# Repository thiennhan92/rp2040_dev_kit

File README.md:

# RP2040 Development Board

This is a custom development board based on the Raspberry Pi RP2040 microcontroller. It integrates essential peripherals for embedded systems prototyping, including USB, Ethernet, RGB LEDs, sensors, and storage. The design is accompanied by validated firmware that supports all core hardware features.

---

## 🧩 Features

- **Microcontroller**: Raspberry Pi RP2040 (dual-core ARM Cortex-M0+)
- **Power Management**:
  - XL1509-3.3 Buck Converter
  - CH217K USB Power Switch
- **USB Interface**:
  - CH340N USB-to-Serial
  - Dual USB ports for host and device roles
- **Networking**:
  - LAN8720A Ethernet PHY (RMII)
  - RJ45 connector (HR911105A)
- **Storage**:
  - MicroSD card 
  - W25Q128FV QSPI Flash
- **Sensors**:
  - ADXL345 3-Axis Accelerometer (I²C/SPI configurable)
- **User Interface**:
  - Daisy-chained WS2812-compatible RGB LEDs
  - Onboard buzzer
  - Status LEDs (Ethernet activity)
- **Debugging**:
  - SWD interface
  - USB bootloader support
- **Expansion**:
  - HDMI-style connector (repurposed for GPIO)
  - Multiple GPIO headers and DIP switches

---

## ✅ Firmware Validation

The firmware has been **fully validated** and supports all major board features.  
*(Please check with Arduino and Pico SDK examples)*

The firmware has been fully validated and supports all major board features:

- [x] **USB Host/Device** – Detection and communication
- [x] **Ethernet** – Connectivity via LAN8720A
- [x] **MicroSD** – FAT filesystem read/write
- [x] **RGB LEDs** – WS2812-compatible LED control
- [x] **ADXL345** – Sensor readout over I²C
- [x] **QSPI Flash** – W25Q128FV access
- [x] **Buzzer & GPIO** – Output control and signal handling
- [x] **HDMI** - Digital video signal rendering tested
- [x] **Bootloader & SWD** – Debugging and firmware upload

© 2025 – RP2040 Dev Board Project. All rights reserved.

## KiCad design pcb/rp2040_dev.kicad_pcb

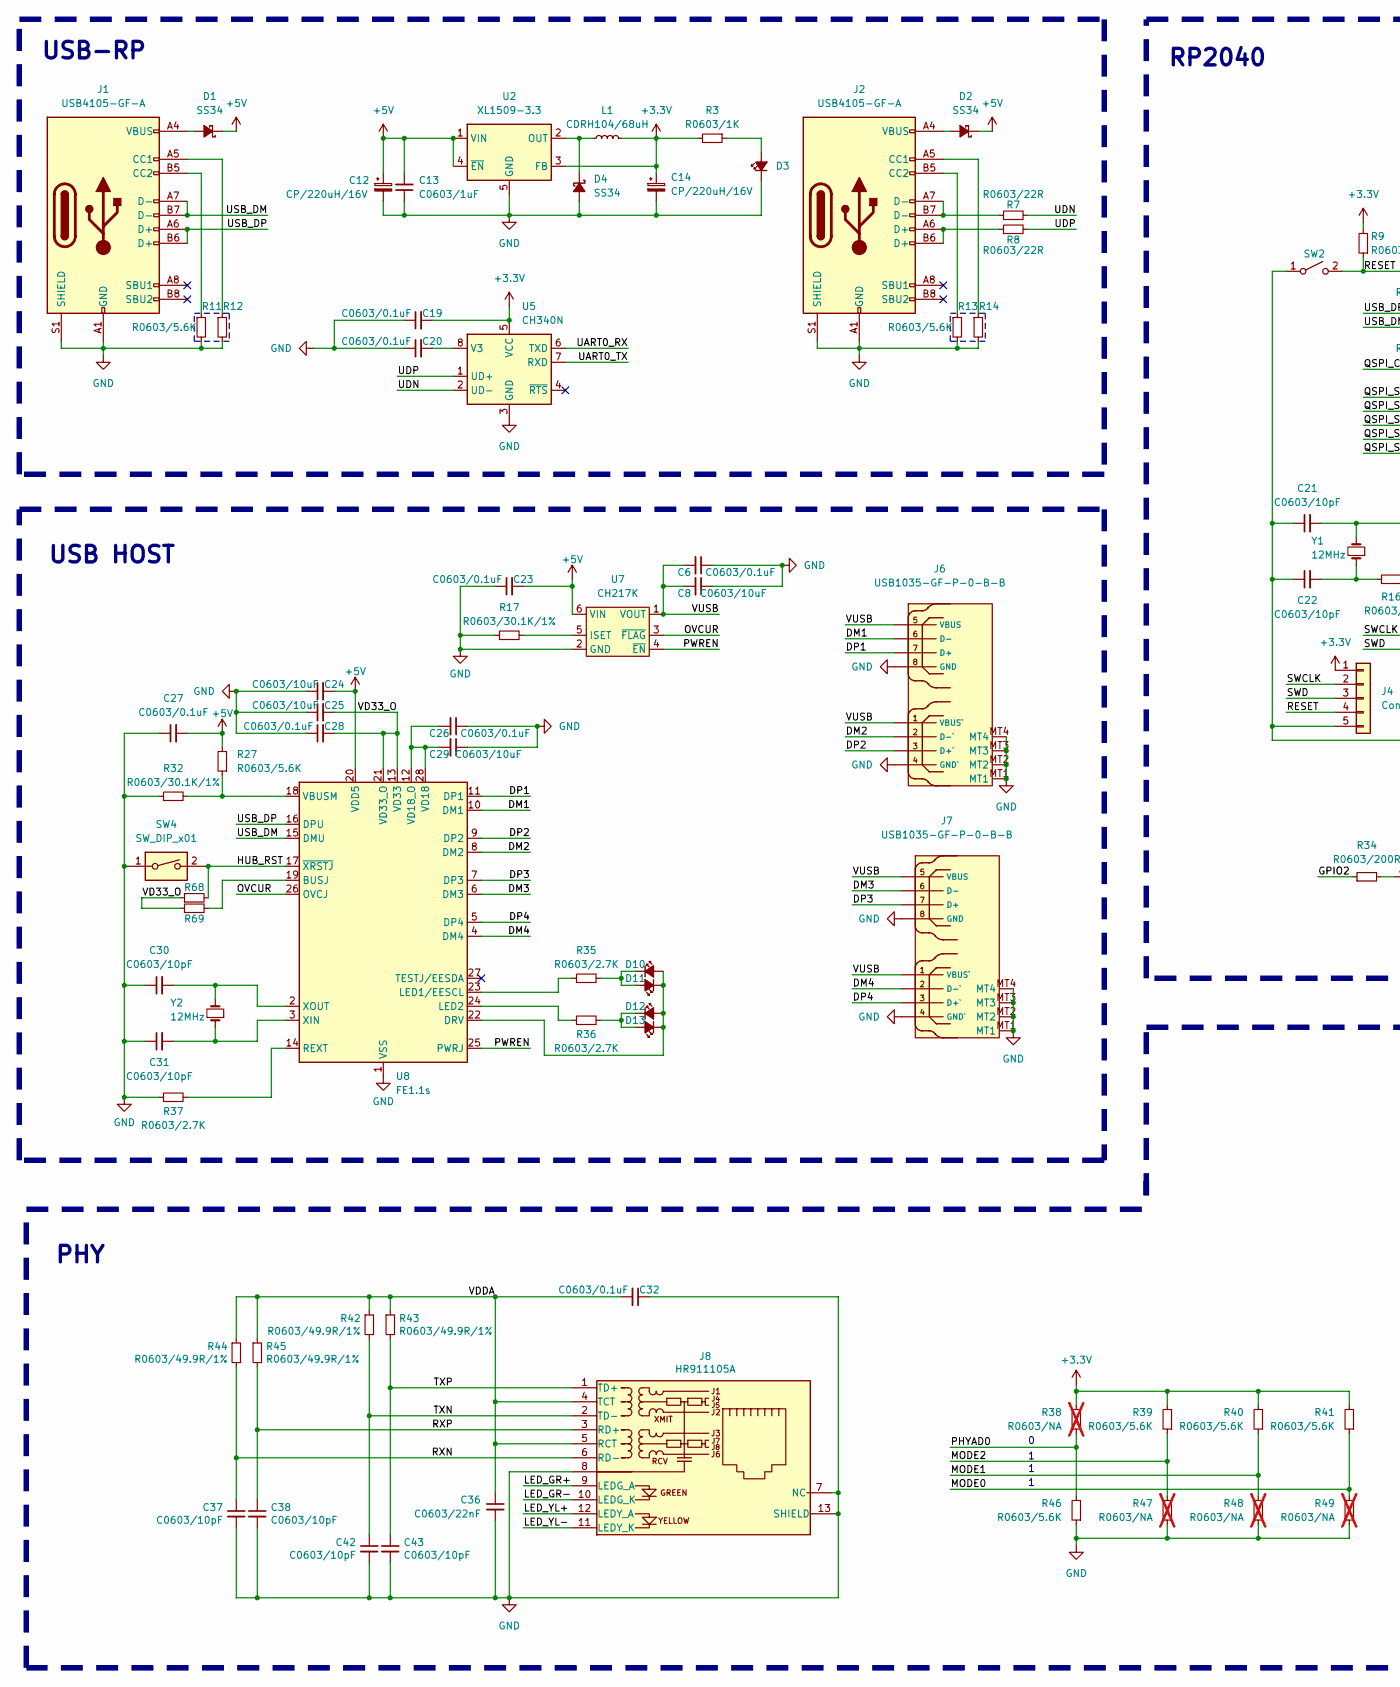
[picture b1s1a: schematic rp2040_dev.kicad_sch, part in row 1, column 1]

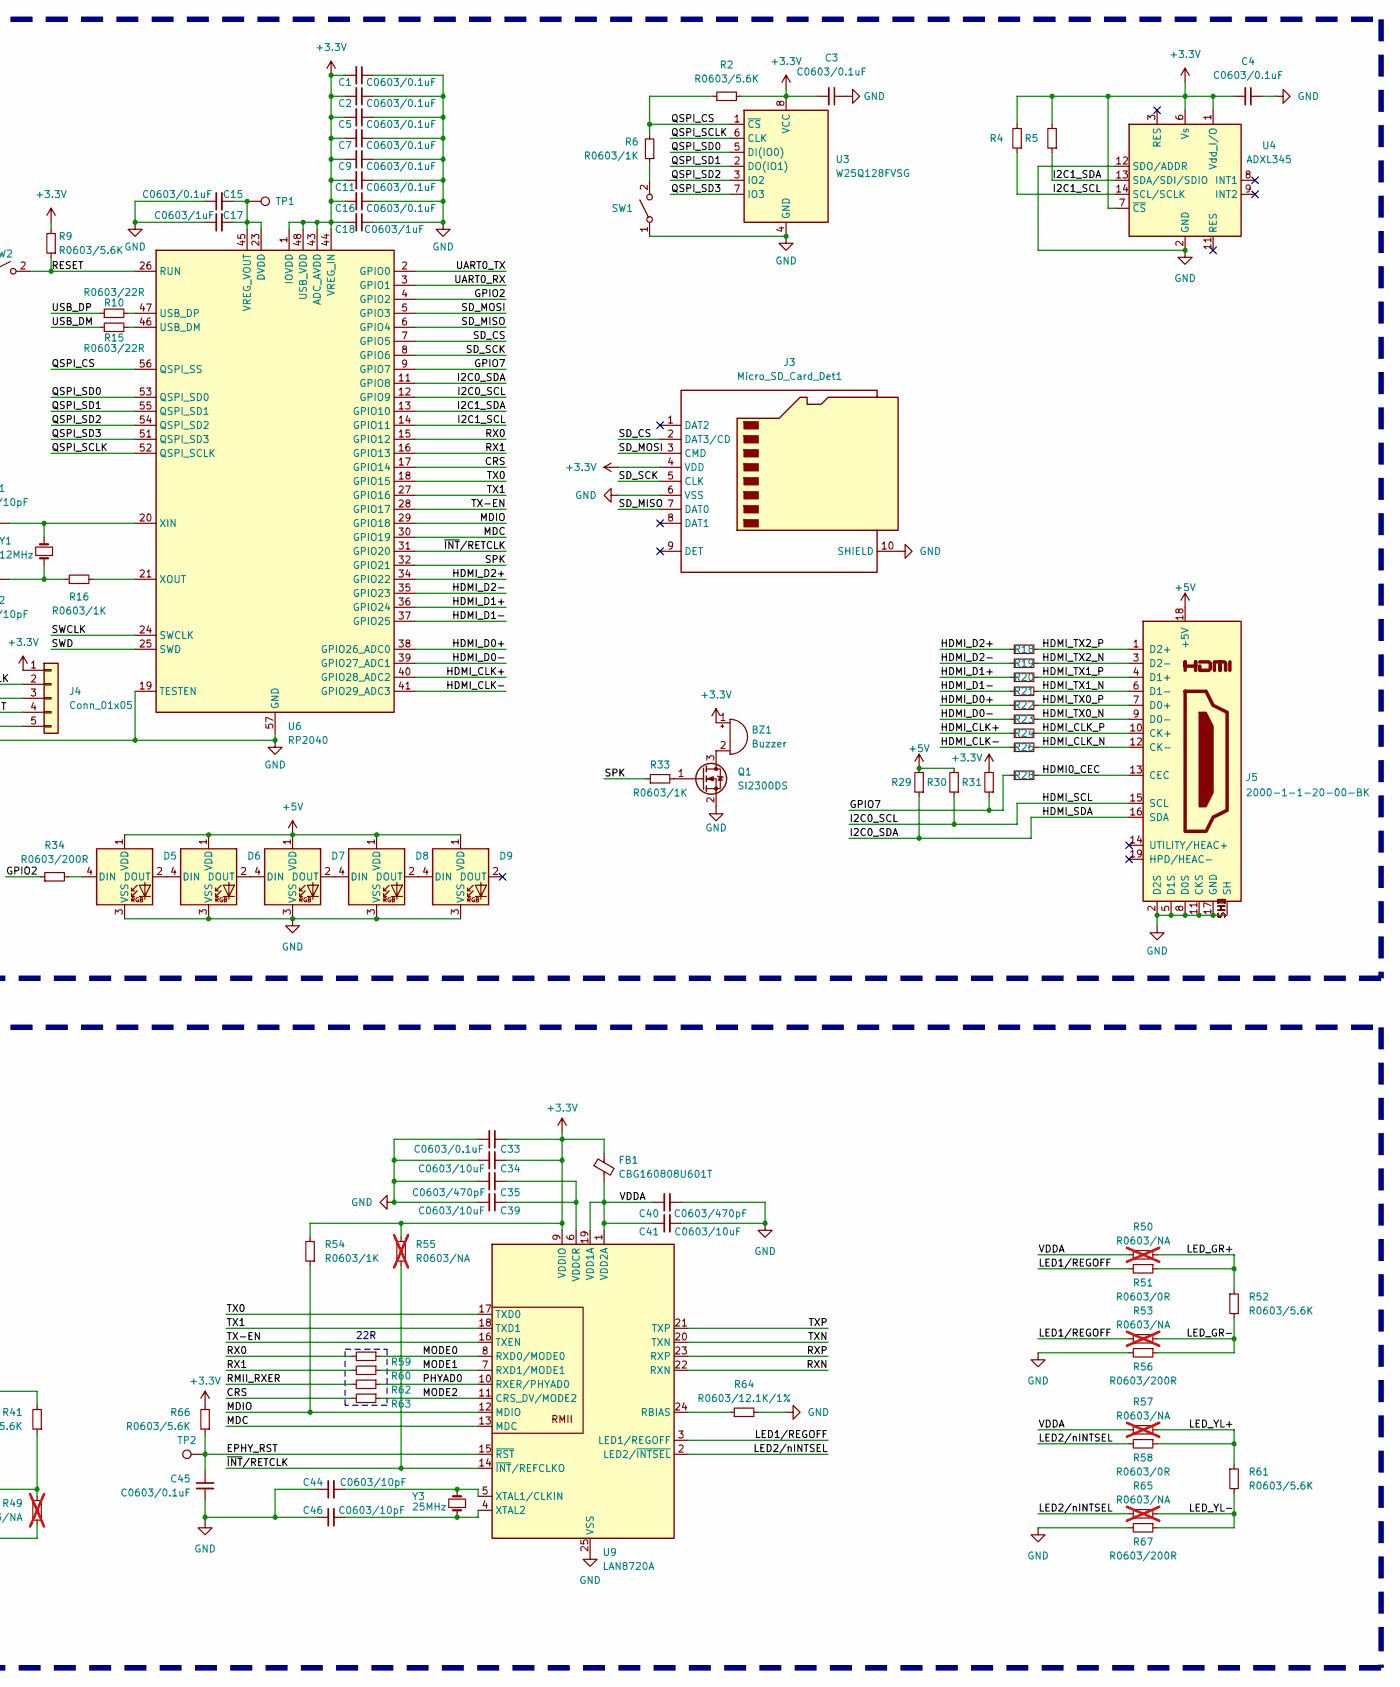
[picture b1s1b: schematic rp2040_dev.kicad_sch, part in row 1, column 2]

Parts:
BZ1: Buzzer; Buzzer_12x9.5RM7.6
C1, C2, C3, C4, C5, C6, C7, C9, C11, C15, C16, C19, C20, C23, C26, C27, C28, C32, C33, C45: C0603/0.1uF; C0603_HandSoldering
C8, C24, C25, C29, C34, C39, C41: C0603/10uF; C0603_HandSoldering
C12, C14: CP/220uH/16V; CP_Elec_6.3x7.7
C13, C17, C18: C0603/1uF; C0603_HandSoldering
C21, C22, C30, C31: C0603/10pF; C0603_HandSoldering; PartNumber 0603N270K250CT
C35, C40: C0603/470pF; C0603_HandSoldering
C36: C0603/22nF; C0603_HandSoldering
C37, C38, C42, C43, C44, C46: C0603/10pF; C0603_HandSoldering
D1, D2, D4: SS34; D_SMA
D3, D10, D11, D12, D13: LED_green; LED_0603_1608Metric
D5, D6, D7, D8, D9: WS2812B; LED_WS2812B_PLCC4_5.0x5.0mm_P3.2mm
FB1: CBG160808U601T; L_0603_1608Metric
J1, J2: USB4105-GF-A; USB_C_Receptacle_GCT_USB4105-xx-A_16P_TopMnt_Horizontal; PartNumber USB4105-GF-A
J3: Micro_SD_Card_Det1; MiSD-PP-9P-V2
J4: Conn_01x05; PinHeader_1x05_P2.54mm_Vertical
J5: 2000-1-1-20-00-BK; CNCTECH_2000-1-1-20-00-BK; PARTREV A
J6, J7: USB1035-GF-P-0-B-B; MOLEX_USB_67298-4090
J8: HR911105A; RJ45_HR911105A
L1: CDRH104/68uH; L_Bourns_SRP1038C_10.0x10.0mm
Q1: SI2300DS; SOT-23; PartNumber SI2302DDS-T1-GE3
R2, R9, R11, R12, R13, R14, R27, R39, R40, R41, R46, R52, R61, R66, R68, R69: R0603/5.6K; R0603_HandSoldering
R3, R6, R16, R33, R54: R0603/1K; R0603_HandSoldering
R4, R5, R29, R30, R31, R35, R36, R37: R0603/2.7K; R0603_HandSoldering
R7, R8, R10, R15, R59, R60, R62, R63: R0603/22R; R0603_HandSoldering
R17, R32: R0603/30.1K/1%; R0603_HandSoldering
R18, R19, R20, R21, R22, R23, R24, R26, R28, R34, R56, R67: R0603/200R; R0603_HandSoldering
R38, R47, R48, R49, R50, R53, R55, R57, R65: R0603/NA; R0603_HandSoldering; not fitted
R42, R43, R44, R45: R0603/49.9R/1%; R0603_HandSoldering
R51, R58: R0603/0R; R0603_HandSoldering
R64: R0603/12.1K/1%; R0603_HandSoldering
SW1, SW2: SW_SPST_3x4mm; SW_SPST_B3U-1000P
SW4: SW_DIP_x01; SW_DIP_SPSTx01_Slide_9.78x4.72mm_W7.62mm_P2.54mm
TP1, TP2: TestPoint; TestPoint_Pad_D1.0mm
U2: XL1509-3.3; SOIC-8_3.9x4.9mm_P1.27mm
U3: W25Q128FVSG; SOIC-8_5.23x5.23mm_P1.27mm; PartNumber W25Q128JVS
U4: ADXL345; LGA-14_3x5mm_P0.8mm_LayoutBorder1x6y
U5: CH340N; SOP-8_3.9x4.9mm_P1.27mm
U6: RP2040; QFN-56-1EP_7x7mm_P0.4mm_EP3.2x3.2mm_ThermalVias; PartNumber RP2040
U7: CH217K; SOT-23-6
U8: FE1.1s; SSOP-28_3.9x9.9mm_P0.635mm
U9: LAN8720A; VQFN-24-1EP_4x4mm_P0.5mm_EP2.5x2.5mm
Y1, Y2: 12MHz; Crystal_SMD_5032-2Pin_5.0x3.2mm
Y3: 25MHz; Crystal_SMD_5032-2Pin_5.0x3.2mm

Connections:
+3.3V: BZ1.1 (-), C1.2, C2.2, C3.2, C4.2, C5.2, C7.2, C9.2, C11.2, C14.1, C16.2, C18.2, C19.2, C33.1, C34.1, FB1.1, J3.4 (VDD), J4.1, L1.2, R2.2, R3.2, R4.2, R5.2, R9.2, R31.2, R38.2, R39.2, R40.2, R41.2, R54.2, R55.2, R66.2, U2.3 (FB), U3.8 (VCC), U4.1 (Vdd_I/O), U4.6 (Vs), U4.7 (~CS), U5.5 (VCC), U6.1 (IOVDD), U6.10 (IOVDD), U6.22 (IOVDD), U6.33 (IOVDD), U6.42 (IOVDD), U6.43 (ADC_AVDD), U6.44 (VREG_IN), U6.48 (USB_VDD), U6.49 (IOVDD), U9.9 (VDDIO)
+5V: C12.1, C13.2, C23.2, C24.2, C27.2, D1.1 (K), D2.1 (K), D5.1 (VDD), D6.1 (VDD), D7.1 (VDD), D8.1 (VDD), D9.1 (VDD), J5.18 (+5V), R27.2, R29.2, R30.2, U2.1 (VIN), U2.4 (~EN), U7.6 (VIN), U8.20 (VDD5)
/CRS: R63.2, U6.17 (GPIO14)
/DM1: J6.6 (D-), U8.10 (DM1)
/DM2: J6.2 (D-`), U8.8 (DM2)
/DM3: J7.6 (D-), U8.6 (DM3)
/DM4: J7.2 (D-`), U8.4 (DM4)
/DP1: J6.7 (D+), U8.11 (DP1)
/DP2: J6.3 (D+`), U8.9 (DP2)
/DP3: J7.7 (D+), U8.7 (DP3)
/DP4: J7.3 (D+`), U8.5 (DP4)
/EPHY_RST: C45.2, R66.1, TP2.1, U9.15 (~RST)
/GPIO2: R34.1, U6.4 (GPIO2)
/GPIO7: R28.1, R31.1, U6.9 (GPIO7)
/HDMI0_CEC: J5.13 (CEC), R28.2
/HDMI_CLK+: R24.1, U6.40 (GPIO28_ADC2)
/HDMI_CLK-: R26.1, U6.41 (GPIO29_ADC3)
/HDMI_CLK_N: J5.12 (CK-), R26.2
/HDMI_CLK_P: J5.10 (CK+), R24.2
/HDMI_D0+: R22.1, U6.38 (GPIO26_ADC0)
/HDMI_D0-: R23.1, U6.39 (GPIO27_ADC1)
/HDMI_D1+: R20.1, U6.36 (GPIO24)
/HDMI_D1-: R21.1, U6.37 (GPIO25)
/HDMI_D2+: R18.1, U6.34 (GPIO22)
/HDMI_D2-: R19.1, U6.35 (GPIO23)
/HDMI_SCL: J5.15 (SCL), R30.1, U6.12 (GPIO9)
/HDMI_SDA: J5.16 (SDA), R29.1, U6.11 (GPIO8)
/HDMI_TX0_N: J5.9 (D0-), R23.2
/HDMI_TX0_P: J5.7 (D0+), R22.2
/HDMI_TX1_N: J5.6 (D1-), R21.2
/HDMI_TX1_P: J5.4 (D1+), R20.2
/HDMI_TX2_N: J5.3 (D2-), R19.2
/HDMI_TX2_P: J5.1 (D2+), R18.2
/HUB_RST: R68.2, SW4.2, U8.17 (~XRSTJ)
/I2C1_SCL: R4.1, U4.14 (SCL/SCLK), U6.14 (GPIO11)
/I2C1_SDA: R5.1, U4.13 (SDA/SDI/SDIO), U6.13 (GPIO10)
/LED1/REGOFF: R51.2, R53.2, U9.3 (LED1/REGOFF)
/LED2/nINTSEL: R58.2, R65.2, U9.2 (LED2/~INTSEL)
/LED_GR+: J8.9 (LEDG_A), R50.1, R51.1, R52.1
/LED_GR-: J8.10 (LEDG_K), R52.2, R53.1, R56.1
/LED_YL+: J8.12 (LEDY_A), R57.1, R58.1, R61.1
/LED_YL-: J8.11 (LEDY_K), R61.2, R65.1, R67.1
/MDC: U6.30 (GPIO19), U9.13 (MDC)
/MDIO: R54.1, U6.29 (GPIO18), U9.12 (MDIO)
/MODE0: R41.1, R49.2, R59.1, U9.8 (RXD0/MODE0)
/MODE1: R40.1, R48.2, R60.1, U9.7 (RXD1/MODE1)
/MODE2: R39.1, R47.2, R63.1, U9.11 (CRS_DV/MODE2)
/OVCUR: U7.3 (~FLAG), U8.26 (OVCJ)
/PHYAD0: R38.1, R46.2, R62.1, U9.10 (RXER/PHYAD0)
/PWREN: U7.4 (~EN), U8.25 (PWRJ)
/QSPI_CS: R2.1, R6.2, U3.1 (~CS), U6.56 (QSPI_SS)
/QSPI_SCLK: U3.6 (CLK), U6.52 (QSPI_SCLK)
/QSPI_SD0: U3.5 (DI(IO0)), U6.53 (QSPI_SD0)
/QSPI_SD1: U3.2 (DO(IO1)), U6.55 (QSPI_SD1)
/QSPI_SD2: U3.3 (IO2), U6.54 (QSPI_SD2)
/QSPI_SD3: U3.7 (IO3), U6.51 (QSPI_SD3)
/RESET: J4.4, R9.1, SW2.2 (B), U6.26 (RUN)
/RMII_RXER: R62.2
/RX0: R59.2, U6.15 (GPIO12)
/RX1: R60.2, U6.16 (GPIO13)
/RXN: C37.1, J8.6 (RD-), R44.2, U9.22 (RXN)
/RXP: C38.1, J8.3 (RD+), R45.2, U9.23 (RXP)
/SD_CS: J3.2 (DAT3/CD), U6.7 (GPIO5)
/SD_MISO: J3.7 (DAT0), U6.6 (GPIO4)
/SD_MOSI: J3.3 (CMD), U6.5 (GPIO3)
/SD_SCK: J3.5 (CLK), U6.8 (GPIO6)
/SPK: R33.1, U6.32 (GPIO21)
/SWCLK: J4.2, U6.24 (SWCLK)
/SWD: J4.3, U6.25 (SWD)
/TX0: U6.18 (GPIO15), U9.17 (TXD0)
/TX1: U6.27 (GPIO16), U9.18 (TXD1)
/TX-EN: U6.28 (GPIO17), U9.16 (TXEN)
/TXN: C42.1, J8.2 (TD-), R42.2, U9.20 (TXN)
/TXP: C43.1, J8.1 (TD+), R43.2, U9.21 (TXP)
/UART0_RX: U5.6 (TXD), U6.3 (GPIO1)
/UART0_TX: U5.7 (RXD), U6.2 (GPIO0)
/UDN: R7.2, U5.2 (UD-)
/UDP: R8.2, U5.1 (UD+)
/USB_DM: J1.A7 (D-), J1.B7 (D-), R15.1, U8.15 (DMU)
/USB_DP: J1.A6 (D+), J1.B6 (D+), R10.1, U8.16 (DPU)
/VD33_O: C25.2, C28.2, R68.1, R69.1, U8.13 (VD33), U8.21 (VD33_O)
/VDDA: C32.2, C36.1, C40.1, C41.1, FB1.2, J8.4 (TCT), J8.5 (RCT), R42.1, R43.1, R44.1, R45.1, R50.2, R57.2, U9.1 (VDD2A), U9.19 (VDD1A)
/VUSB: C6.2, C8.2, J6.1 (VBUS`), J6.5 (VBUS), J7.1 (VBUS`), J7.5 (VBUS), U7.1 (VOUT)
/~INT/RETCLK: R55.1, U6.31 (GPIO20), U9.14 (~INT/REFCLKO)
GND: C1.1, C2.1, C3.1, C4.1, C5.1, C6.1, C7.1, C8.1, C9.1, C11.1, C12.2, C13.1, C14.2, C15.1, C16.1, C17.1, C18.1, C19.1, C20.1, C21.1, C22.1, C23.1, C24.1, C25.1, C26.1, C27.1, C28.1, C29.1, C30.1, C31.1, C32.1, C33.2, C34.2, C35.2, C36.2, C37.2, C38.2, C39.2, C40.2, C41.2, C42.2, C43.2, C44.1, C45.1, C46.1, D3.1 (K), D4.2 (A), D5.3 (VSS), D6.3 (VSS), D7.3 (VSS), D8.3 (VSS), D9.3 (VSS), J1.A1 (GND), J1.A12 (GND), J1.B1 (GND), J1.B12 (GND), J1.S1 (SHIELD), J2.A1 (GND), J2.A12 (GND), J2.B1 (GND), J2.B12 (GND), J2.S1 (SHIELD), J3.6 (VSS), J3.10 (SHIELD), J4.5, J5.2 (D2S), J5.5 (D1S), J5.8 (D0S), J5.11 (CKS), J5.17 (GND), J5.SH1 (SH), J5.SH2 (SH), J5.SH3 (SH), J5.SH4 (SH), J6.4 (GND`), J6.8 (GND), J6.MT1, J6.MT2, J6.MT3, J6.MT4, J7.4 (GND`), J7.8 (GND), J7.MT1, J7.MT2, J7.MT3, J7.MT4, J8.7 (NC), J8.8, J8.13 (SHIELD), Q1.2 (S), R11.2, R12.2, R13.2, R14.2, R17.1, R32.1, R37.1, R46.1, R47.1, R48.1, R49.1, R56.2, R64.2, R67.2, SW1.1 (A), SW2.1 (A), SW4.1, U2.5 (GND), U2.6 (GND), U2.7 (GND), U2.8 (GND), U3.4 (GND), U4.2 (GND), U4.4 (GND), U4.5 (GND), U4.12 (SDO/ADDR), U5.3 (GND), U6.19 (TESTEN), U6.57 (GND), U7.2 (GND), U8.1 (VSS), U9.25 (VSS)
unnamed: BZ1.2 (+), Q1.3 (D)
unnamed: C22.2, R16.1, Y1.1
unnamed: D1.2 (A), J1.A4 (VBUS), J1.A9 (VBUS), J1.B4 (VBUS), J1.B9 (VBUS)
unnamed: D2.2 (A), J2.A4 (VBUS), J2.A9 (VBUS), J2.B4 (VBUS), J2.B9 (VBUS)
unnamed: D3.2 (A), R3.1
unnamed: D4.1 (K), L1.1, U2.2 (OUT)
unnamed: D5.4 (DIN), R34.2
unnamed: D5.2 (DOUT), D6.4 (DIN)
unnamed: D6.2 (DOUT), D7.4 (DIN)
unnamed: D7.2 (DOUT), D8.4 (DIN)
unnamed: D8.2 (DOUT), D9.4 (DIN)
unnamed: D10.2 (A), D11.1 (K), D12.2 (A), D13.1 (K), U8.22 (DRV)
unnamed: D10.1 (K), D11.2 (A), R35.2
unnamed: D12.1 (K), D13.2 (A), R36.2
unnamed: J1.A5 (CC1), R12.1
unnamed: J1.B5 (CC2), R11.1
unnamed: J2.A5 (CC1), R14.1
unnamed: J2.B5 (CC2), R13.1
unnamed: J2.A6 (D+), J2.B6 (D+), R8.1
unnamed: J2.A7 (D-), J2.B7 (D-), R7.1
unnamed: Q1.1 (G), R33.2
unnamed: R6.1, SW1.2 (B)
unnamed: C20.2, U5.8 (V3)
unnamed: R15.2, U6.46 (USB_DM)
unnamed: R10.2, U6.47 (USB_DP)
unnamed: C15.2, C17.2, TP1.1, U6.23 (DVDD), U6.45 (VREG_VOUT), U6.50 (DVDD)
unnamed: C21.2, U6.20 (XIN), Y1.2
unnamed: R16.2, U6.21 (XOUT)
unnamed: R17.2, U7.5 (ISET)
unnamed: R69.2, U8.19 (BUSJ)
unnamed: R35.1, U8.23 (LED1/EESCL)
unnamed: R36.1, U8.24 (LED2)
unnamed: R37.2, U8.14 (REXT)
unnamed: R27.1, R32.2, U8.18 (VBUSM)
unnamed: C26.2, C29.2, U8.12 (VD18_O), U8.28 (VD18)
unnamed: C31.2, U8.3 (XIN), Y2.1
unnamed: C30.2, U8.2 (XOUT), Y2.2
unnamed: R64.1, U9.24 (RBIAS)
unnamed: C35.1, C39.1, U9.6 (VDDCR)
unnamed: C44.2, U9.5 (XTAL1/CLKIN), Y3.2
unnamed: C46.2, U9.4 (XTAL2), Y3.1

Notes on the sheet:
22R
RP2040
PHY
USB HOST
USB-RP

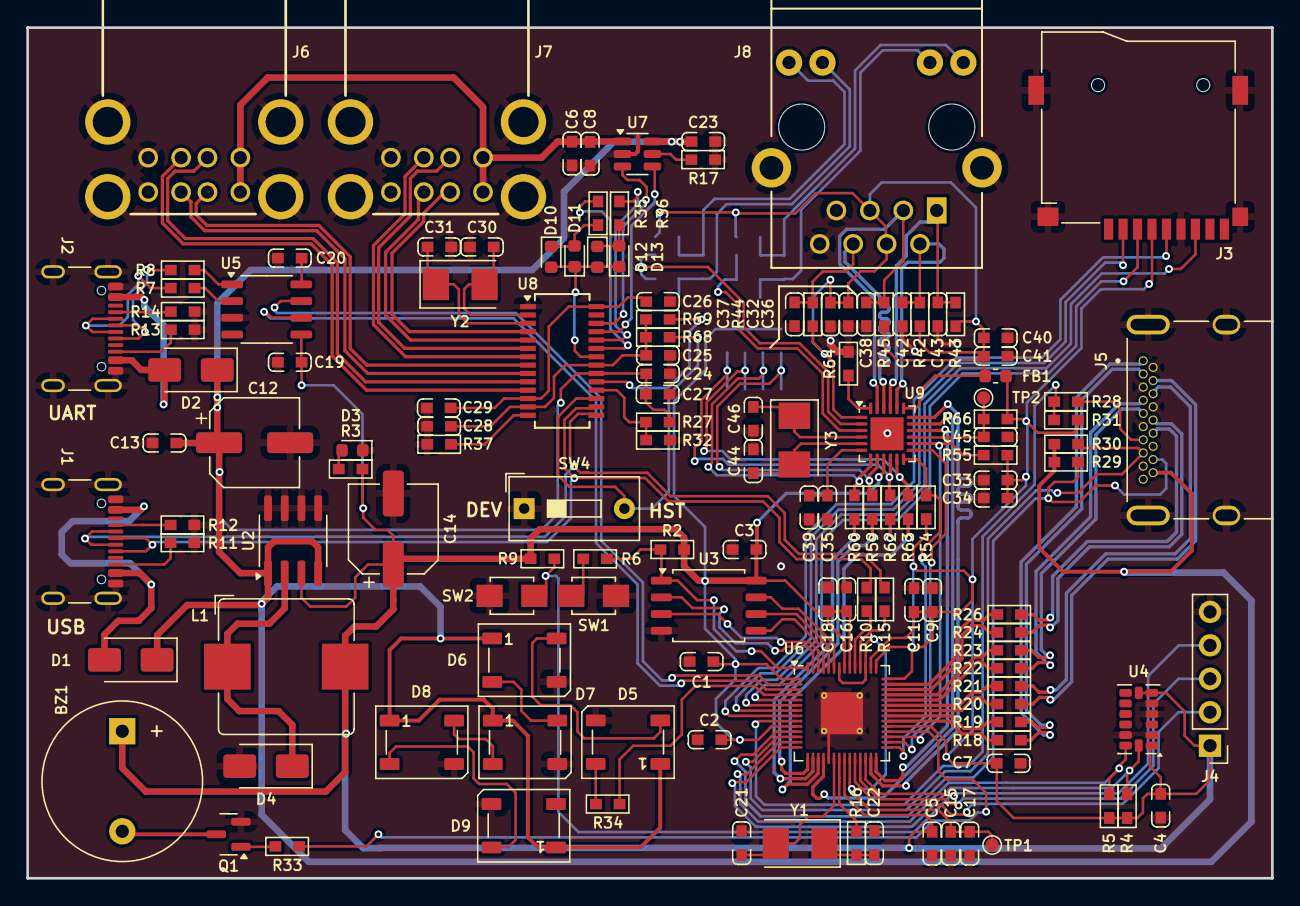
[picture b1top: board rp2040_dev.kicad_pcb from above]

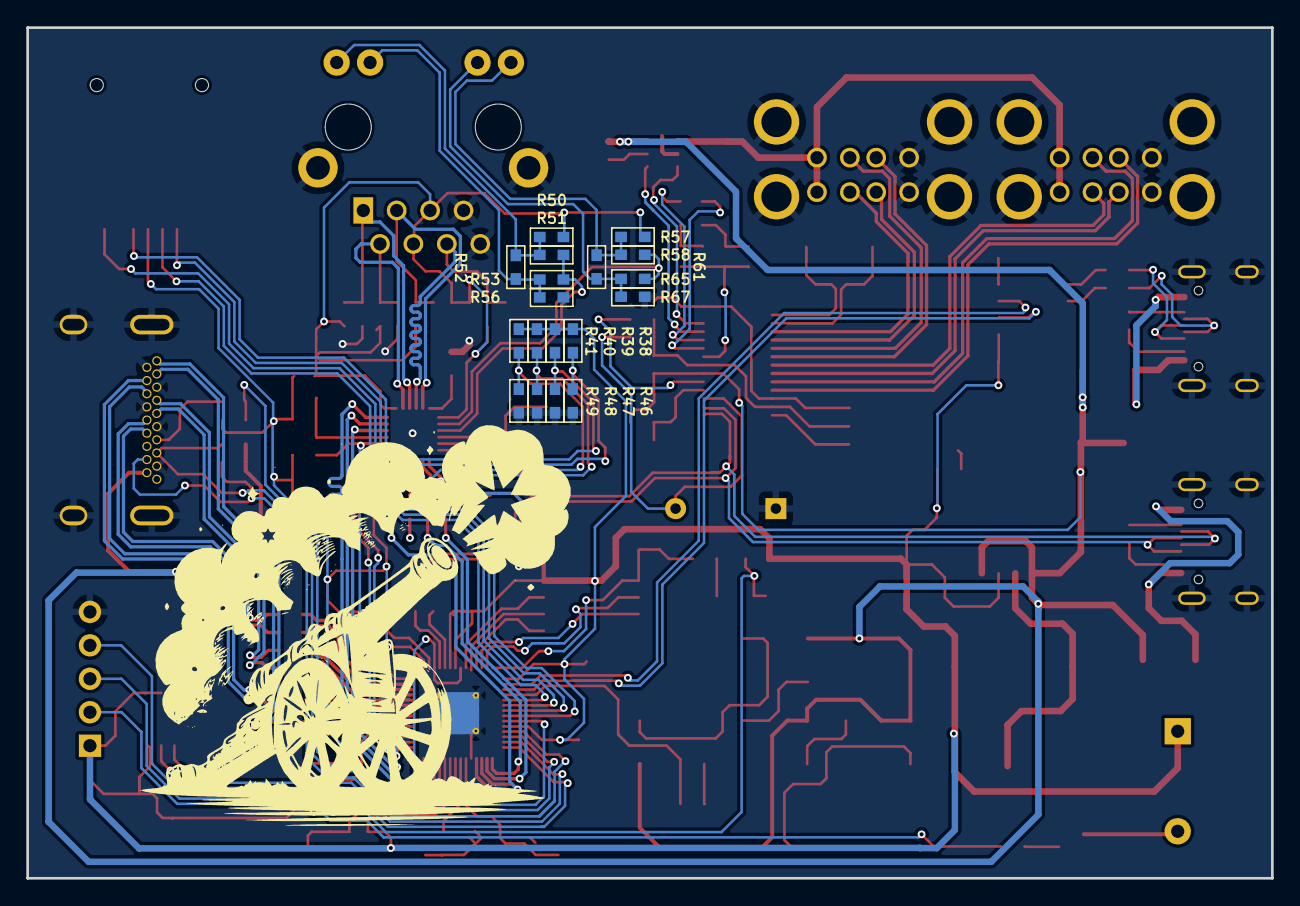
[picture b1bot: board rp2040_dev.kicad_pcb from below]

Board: 2 copper layers, 94.6 x 64.6 mm, 153 parts (18 on the bottom side), 125 nets.

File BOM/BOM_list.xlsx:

Id | Designator | Footprint | Quantity | Designation
1 | SW2,SW1 | SW_SPST_B3U-1000P | 2 | SW_SPST_3x4mm | https://www.thegioiic.com/nut-nhan-3x4mm-cao-2-5mm-2-chan-smd
2 | Y2,Y1 | Crystal_SMD_5032-2Pin_5.0x3.2mm | 2 | 12MHz
3 | Y3 | Crystal_SMD_5032-2Pin_5.0x3.2mm | 1 | 25MHz
4 | BZ1 | Buzzer_12x9.5RM7.6 | 1 | Buzzer 1209
5 | L1 | L_Bourns_SRP1038C_10.0x10.0mm | 1 | CDRH104/68uH
6 | Q1 | SOT-23 | 1 | SI2300DS
7 | SW4 | SW_DIP_01_Slide_W7.62mm_P2.54mm | 1 | SW_DIP_x01
8 | FB1 | L_0603_1608Metric | 1 | CBG160808U601T
9 | U2 | SOIC-8_3.9x4.9mm_P1.27mm | 1 | XL1509-3.3
10 | U3 | SOIC-8_5.23x5.23mm_P1.27mm | 1 | W25Q128FVSG
11 | U4 | LGA-14_3x5mm_P0.8mm | 1 | ADXL345
12 | U5 | SOP-8_3.9x4.9mm_P1.27mm | 1 | CH340N
13 | U6 | QFN-56-1EP_7x7mm_P0.4mm | 1 | RP2040
14 | U7 | SOT-23-6 | 1 | CH217K | https://linhkienthuduc.com/san-pham/ch217k-ic-bao-ve-usb-cur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
15 | U8 | SSOP-28_3.9x9.9mm_P0.635mm | 1 | FE1.1s | https://shopee.vn/product/1152770645/24613658217?gads_t_sig=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
16 | U9 | VQFN-24-1EP_4x4mm_P0.5mm | 1 | LAN8720A
17 | J1,J2 | USB_C_Receptacle_GCT_USB4105 | 2 | USB4105-GF-A | https://www.thegioiic.com/cong-usb-cai-3-1-type-c-16-chan-th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
18 | J3 | MiSD-PP-9P-V2 | 1 | Micro_SD_Card | https://www.thegioiic.com/misd-pp-9p-v2-khay-the-nho-microsd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
19 | J5 | CNCTECH_2000-1-1-20-00-BK | 1 | 10029449-111RLF | https://www.thegioiic.com/cong-hdmi-cai-type-a-19-chan-vuong-goc
20 | J7,J6 | MOLEX_USB_67298-4090 | 2 | USB1035-GF-P-0-B-B | https://www.thegioiic.com/cong-usb-cai-doi-2-0-type-a-8-chan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
21 | J8 | RJ45_HR911105A | 1 | HR911105A
22 | C32,C26,C15,C5,C23,C28,C19,C3,C16,C33,C1,C2,C45, C11,C7,C27,C4,C6,C9,C20 | C0603_HandSoldering | 20 | C0603/0.1uF
23 | C41,C29,C34,C24,C39,C8,C25 | C0603_HandSoldering | 7 | C0603/10uF
24 | C21,C44,C38,C30,C46,C31,C42,C22,C37,C43 | C0603_HandSoldering | 10 | C0603/10pF
25 | C12,C14 | CP_Elec_6.3x7.7 | 2 | CP/220uH/16V
26 | C18,C17,C13 | C0603_HandSoldering | 3 | C0603/1uF
27 | C36 | C0603_HandSoldering | 1 | C0603/22nF
28 | C40,C35 | C0603_HandSoldering | 2 | C0603/470pF
29 | D1,D4,D2 | D_SMA | 3 | SS34
30 | D8,D9,D7,D6,D5 | LED_WS2812B_PLCC4_5.0x5.0mm | 5 | WS2812B
31 | D10,D13,D12,D3,D11 | LED_0603_1608Metric | 5 | LED_green
32 | R62,R7,R63,R10,R60,R15,R8,R59 | R0603_HandSoldering | 8 | R0603/22R
33 | R34,R24,R18,R19,R28,R26,R20,R22,R23,R21,R56,R67 | R0603_HandSoldering | 12 | R0603/200R
34 | R11,R14,R68,R27,R2,R9,R13,R12,R69,R66,R46,R52, R41,R39,R40,R61 | R0603_HandSoldering | 16 | R0603/5.6K
35 | R29,R36,R30,R31,R37,R35,R4,R5 | R0603_HandSoldering | 8 | R0603/2.7K
36 | R6,R3,R54,R33,R16 | R0603_HandSoldering | 5 | R0603/1K
37 | R64 | R0603_HandSoldering | 1 | R0603/12.1K/1%
38 | R32,R17 | R0603_HandSoldering | 2 | R0603/30.1K/1%
39 | R44,R43,R45,R42 | R0603_HandSoldering | 4 | R0603/49.9R/1%
40 | R58,R51 | R0603_HandSoldering | 2 | R0603/0R
41 | R55,R48,R38,R53,R49,R50,R47,R65,R57 | R0603_HandSoldering | 9 | R0603/NA

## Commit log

2025-03-11 Initial project
2025-03-18 Update BOM list
2025-07-31 Fix UART0 reversed pins
2025-08-04 Update Readme file
2025-08-04 Add board image
